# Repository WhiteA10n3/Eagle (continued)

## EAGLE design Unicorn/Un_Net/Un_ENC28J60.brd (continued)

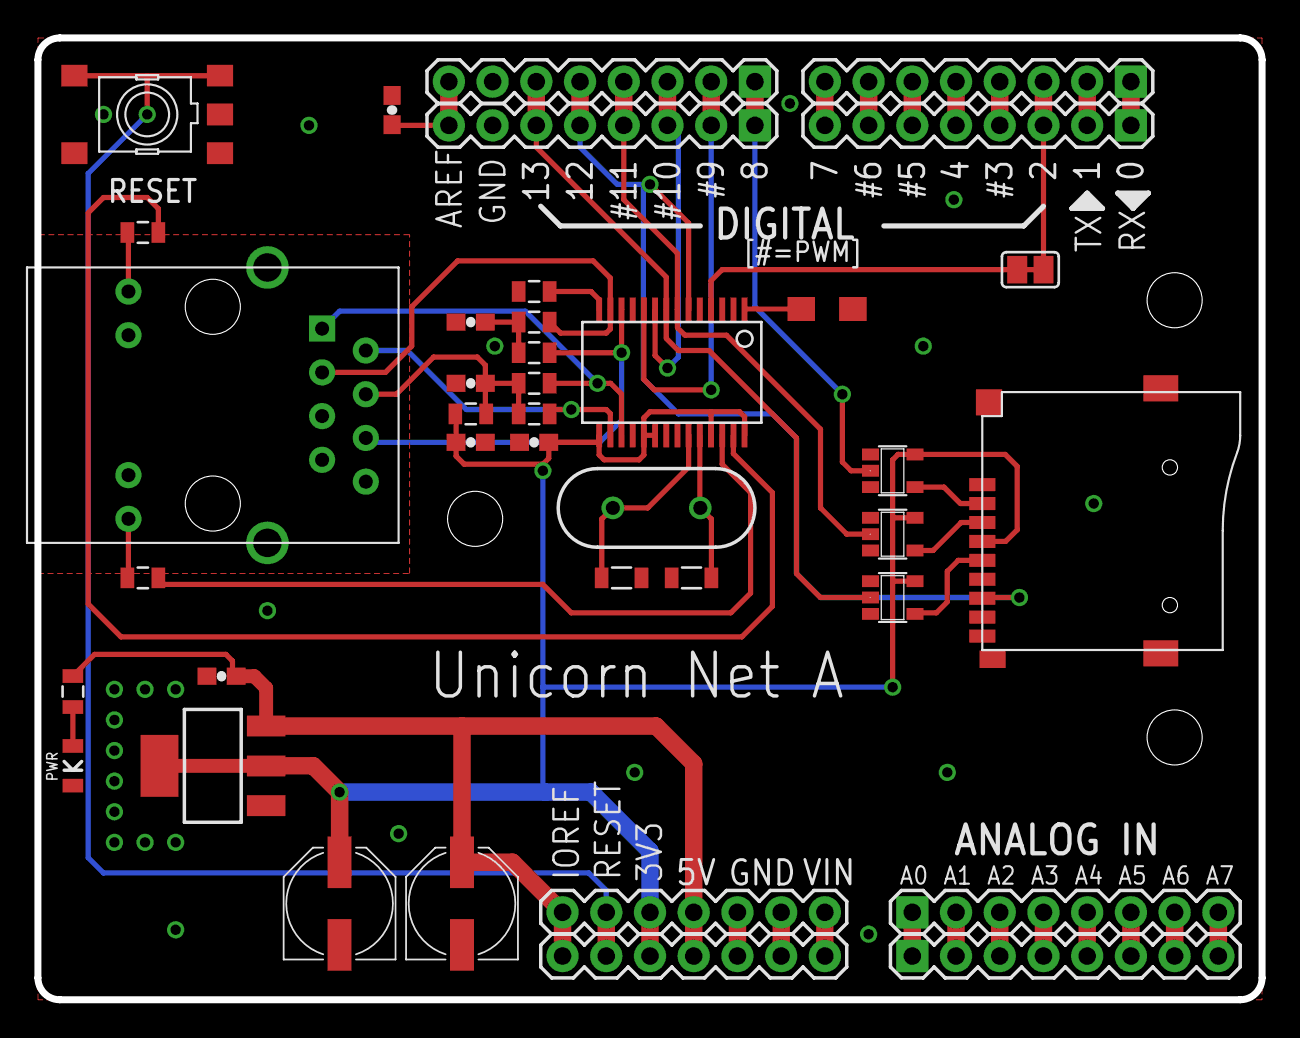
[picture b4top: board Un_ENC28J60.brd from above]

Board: 2 copper layers, 71.1 x 55.9 mm, 39 parts (0 on the bottom side), 46 nets.

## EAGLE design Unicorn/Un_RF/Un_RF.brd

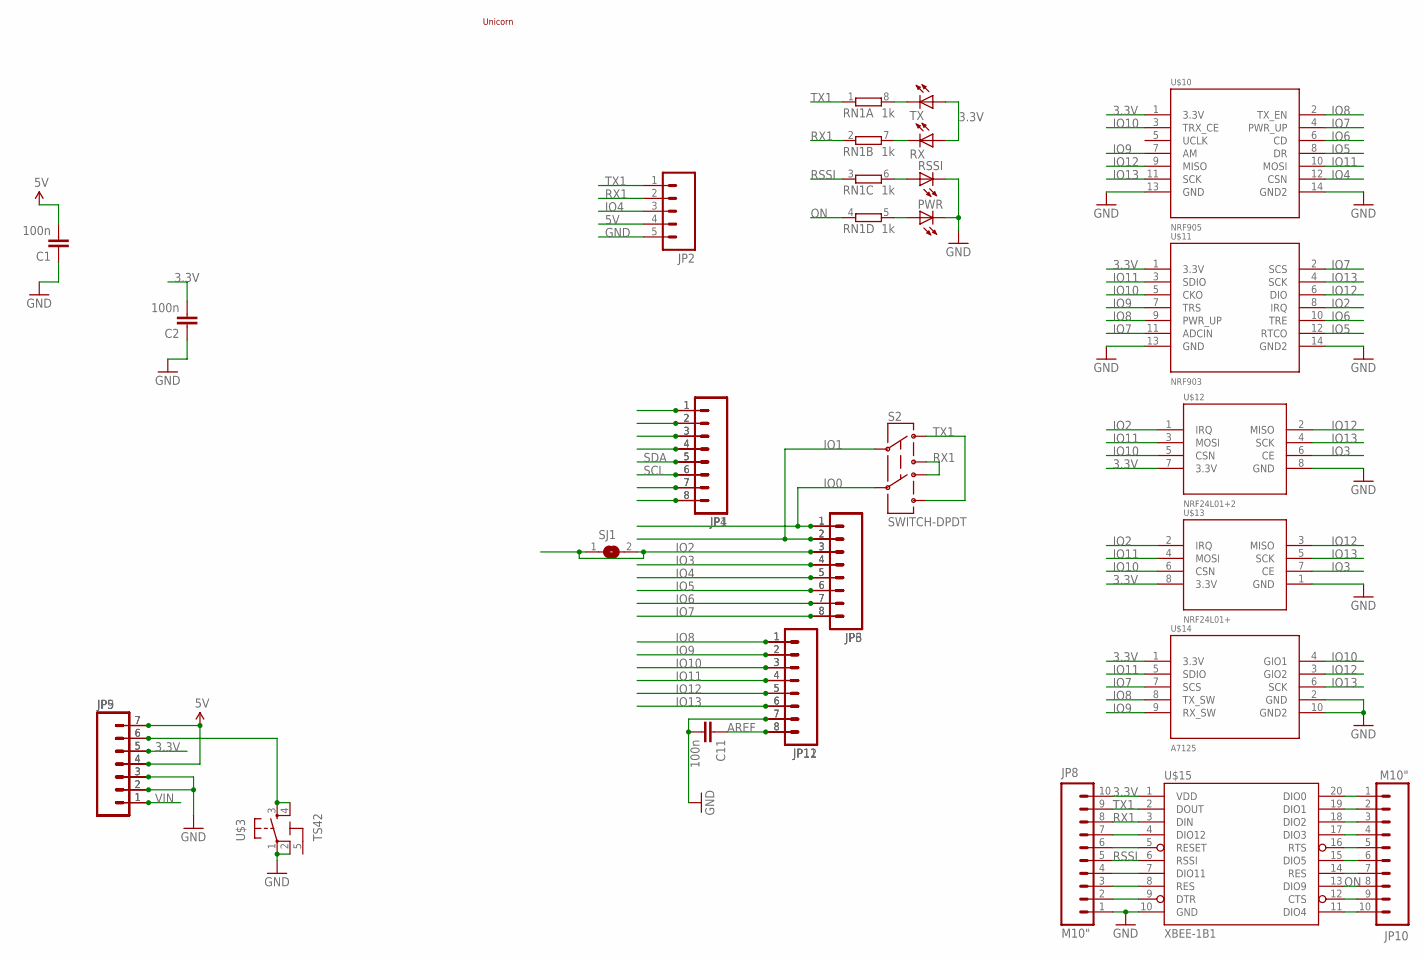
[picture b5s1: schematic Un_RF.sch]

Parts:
C1, C2, C11: 100n; 0603-CAP
JP1, JP4, JP11, JP12: M081X08; 1X08
JP2: M05PTH; 1X05
JP3, JP6: M08; 1X08
JP5, JP9: M07; 1X07
JP8, JP10: M10"; 1X10
PWR: LED0805; LED-0805
RN1: 1k; CAY16
RSSI: LED0805; LED-0805
RX: LED0805; LED-0805
S2: SWITCH-DPDT; SWITCH-P2
SJ1: SJ
TX: LED0805; LED-0805
U$3: TS42
U$4: UNICORN; UNICORN_1
U$10: NRF905; 2X7
U$11: NRF903; 2X7
U$12: NRF24L01+2; 2X4
U$13: NRF24L01+; 1X08
U$14: A7125; 1X10-2MM
U$15: XBEE-1B1; XBEE-1

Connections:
3.3V: C2.2, JP5.5, JP8.10, JP9.5, RX.1 (A), TX.1 (A), U$10.1 (3.3V), U$11.1 (3.3V), U$12.7 (3.3V), U$13.8 (3.3V), U$14.1 (3.3V), U$15.1 (VDD)
5V: C1.2, JP2.4, JP5.4, JP5.7, JP9.4, JP9.7
A0: JP1.1, JP4.1
AREF: C11.1, JP11.8, JP12.8
GND: C1.1, C2.1, C11.2, JP2.5, JP5.2, JP5.3, JP8.1, JP9.2, JP9.3, JP11.7, JP12.7, PWR.2 (C), RSSI.2 (C), U$3.1, U$3.2, U$10.13 (GND), U$10.14 (GND2), U$11.13 (GND), U$11.14 (GND2), U$12.8 (GND), U$13.1 (GND), U$14.2 (GND), U$14.10 (GND2), U$15.10 (GND)
IO0: JP3.1, JP6.1, S2.5
IO1: JP3.2, JP6.2, S2.2
IO2: JP3.3, JP6.3, SJ1.1, SJ1.2, U$11.8 (IRQ), U$12.1 (IRQ), U$13.2 (IRQ)
IO3: JP3.4, JP6.4, U$12.6 (CE), U$13.7 (CE)
IO4: JP2.3, JP3.5, JP6.5, U$10.12 (CSN)
IO5: JP3.6, JP6.6, U$10.8 (DR), U$11.12 (RTCO)
IO6: JP3.7, JP6.7, U$10.6 (CD), U$11.10 (TRE)
IO7: JP3.8, JP6.8, U$10.4 (PWR_UP), U$11.2 (SCS), U$11.11 (ADCIN), U$14.7 (SCS)
IO8: JP11.1, JP12.1, U$10.2 (TX_EN), U$11.9 (PWR_UP), U$14.8 (TX_SW)
IO9: JP11.2, JP12.2, U$10.7 (AM), U$11.7 (TRS), U$14.9 (RX_SW)
IO10: JP11.3, JP12.3, U$10.3 (TRX_CE), U$11.5 (CKO), U$12.5 (CSN), U$13.6 (CSN), U$14.4 (GIO1)
IO11: JP11.4, JP12.4, U$10.10 (MOSI), U$11.3 (SDIO), U$12.3 (MOSI), U$13.4 (MOSI), U$14.5 (SDIO)
IO12: JP11.5, JP12.5, U$10.9 (MISO), U$11.6 (DIO), U$12.2 (MISO), U$13.3 (MISO), U$14.3 (GIO2)
IO13: JP11.6, JP12.6, U$10.11 (SCK), U$11.4 (SCK), U$12.4 (SCK), U$13.5 (SCK), U$14.6 (SCK)
unnamed: RN1.8 (2), TX.2 (C)
unnamed: RN1.7 (2), RX.2 (C)
unnamed: RN1.6 (2), RSSI.1 (A)
unnamed: PWR.1 (A), RN1.5 (2)
unnamed: JP10.1, U$15.20 (DIO0)
unnamed: JP1.7, JP4.7
unnamed: JP1.8, JP4.8
unnamed: JP10.2, U$15.19 (DIO1)
unnamed: JP10.3, U$15.18 (DIO2)
unnamed: JP10.4, U$15.17 (DIO3)
unnamed: JP1.2, JP4.2
unnamed: JP1.3, JP4.3
unnamed: JP1.4, JP4.4
unnamed: JP10.5, U$15.16 (RTS)
unnamed: JP10.6, U$15.15 (DIO5)
unnamed: JP10.7, U$15.14 (RES)
unnamed: JP5.6, JP9.6, U$3.3, U$3.4
unnamed: JP10.9, U$15.12 (CTS)
unnamed: JP10.10, U$15.11 (DIO4)
unnamed: JP8.2, U$15.9 (DTR)
unnamed: JP8.3, U$15.8 (RES)
unnamed: JP8.4, U$15.7 (DIO11)
unnamed: JP8.6, U$15.5 (RESET)
unnamed: JP8.7, U$15.4 (DIO12)
ON: JP10.8, RN1.4 (1), U$15.13 (DIO9)
RSSI: JP8.5, RN1.3 (1), U$15.6 (RSSI)
RX1: JP2.2, JP8.8, RN1.2 (1), S2.3, S2.4, U$15.3 (DIN)
SCL: JP1.6, JP4.6
SDA: JP1.5, JP4.5
TX1: JP2.1, JP8.9, RN1.1, S2.1, S2.6, U$15.2 (DOUT)
VIN: JP5.1, JP9.1

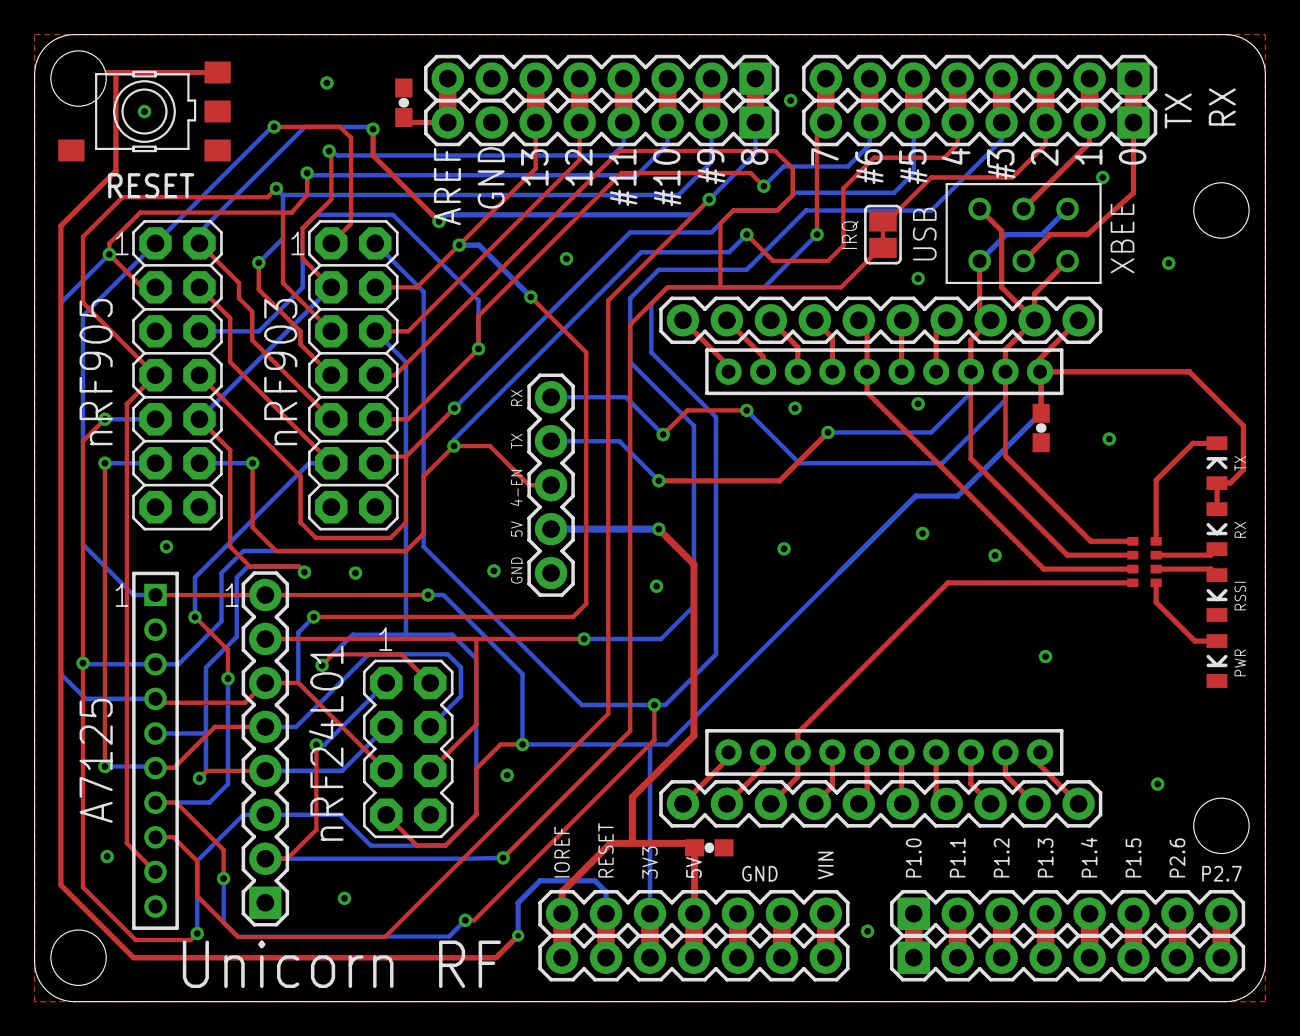
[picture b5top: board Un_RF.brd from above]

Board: 2 copper layers, 71.1 x 55.9 mm, 29 parts (0 on the bottom side), 50 nets.

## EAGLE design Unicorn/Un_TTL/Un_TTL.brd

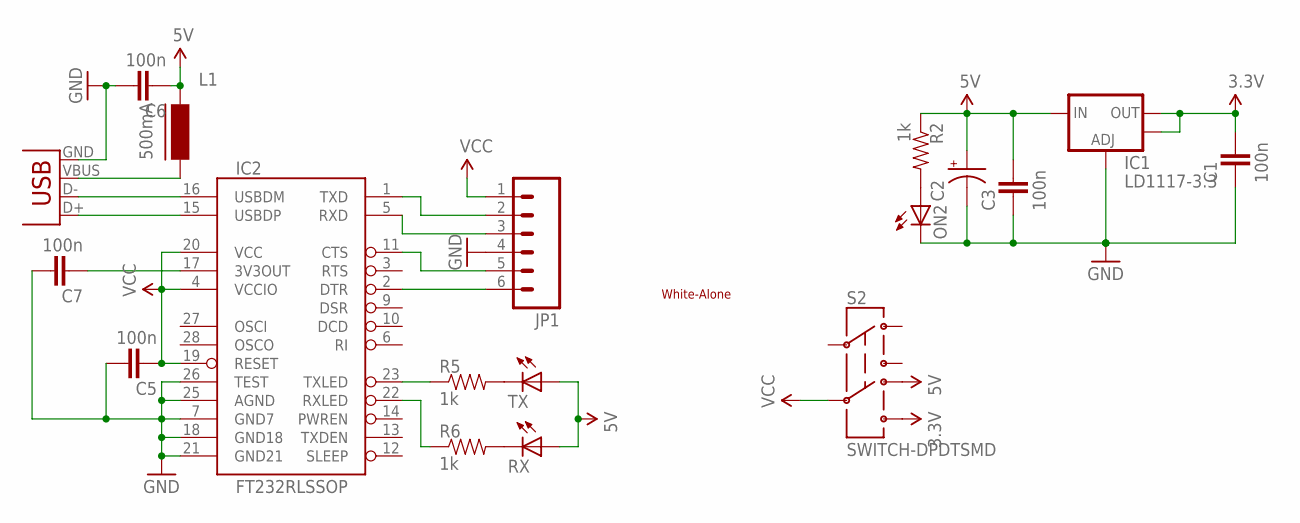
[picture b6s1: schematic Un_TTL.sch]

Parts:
C1, C3, C5, C6, C7: 100n; 0603-CAP
C2: CAP_POL1206; EIA3216
IC1: LD1117-3.3; SOT223
IC2: FT232RLSSOP; SSOP28DB
JP1: M06SIP; 1X06
L1: 500mA; FB805
ON2: LED0805; LED-0805
R2, R5, R6: 1k; 0603-RES
RX: LED0805; LED-0805
S2: SWITCH-DPDTSMD; AYZ0202
TX: LED0805; LED-0805
U$2: WHITE-ALONE_0
X1: USBSMD; USB-MINIB

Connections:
3.3V: C1.1, IC1.2 (OUT), IC1.4 (OUT), S2.6
5V: C2.A (+), C3.1, C6.2, IC1.3 (IN), L1.1, R2.1, RX.1 (A), S2.4, TX.1 (A)
DTR: IC2.11 (CTS), JP1.5
GND: C1.2, C2.C (-), C3.2, C5.1, C6.1, C7.1, IC1.1 (ADJ), IC2.7 (GND7), IC2.18 (GND18), IC2.21 (GND21), IC2.25 (AGND), IC2.26 (TEST), JP1.4, ON2.2 (C), X1.GND
unnamed: ON2.1 (A), R2.2
unnamed: L1.2, X1.VBUS
unnamed: IC2.2 (DTR), JP1.6
unnamed: IC2.16 (USBDM), X1.D-
unnamed: IC2.15 (USBDP), X1.D+
unnamed: IC2.23 (TXLED), R5.1
unnamed: R5.2, TX.2 (C)
unnamed: R6.2, RX.2 (C)
unnamed: IC2.22 (RXLED), R6.1
unnamed: C7.2, IC2.17 (3V3OUT)
RXD: IC2.5 (RXD), JP1.3
TXD: IC2.1 (TXD), JP1.2
VCC: C5.2, IC2.4 (VCCIO), IC2.19 (RESET), IC2.20 (VCC), JP1.1, S2.5

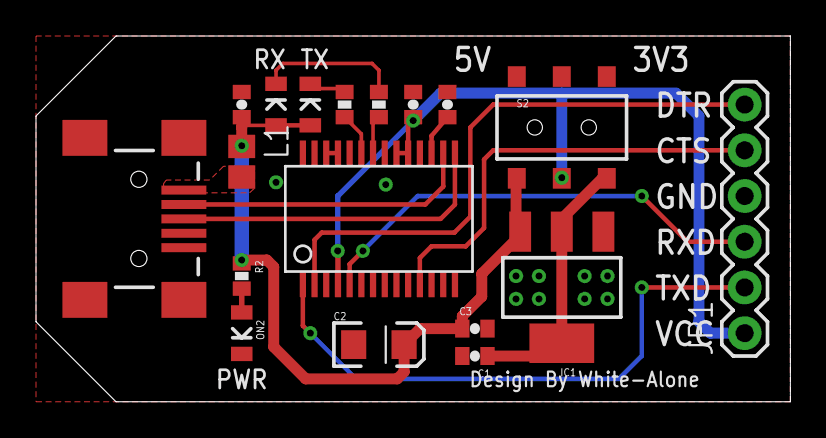
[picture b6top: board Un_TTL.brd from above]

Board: 2 copper layers, 41.9 x 20.3 mm, 19 parts (1 on the bottom side), 17 nets.

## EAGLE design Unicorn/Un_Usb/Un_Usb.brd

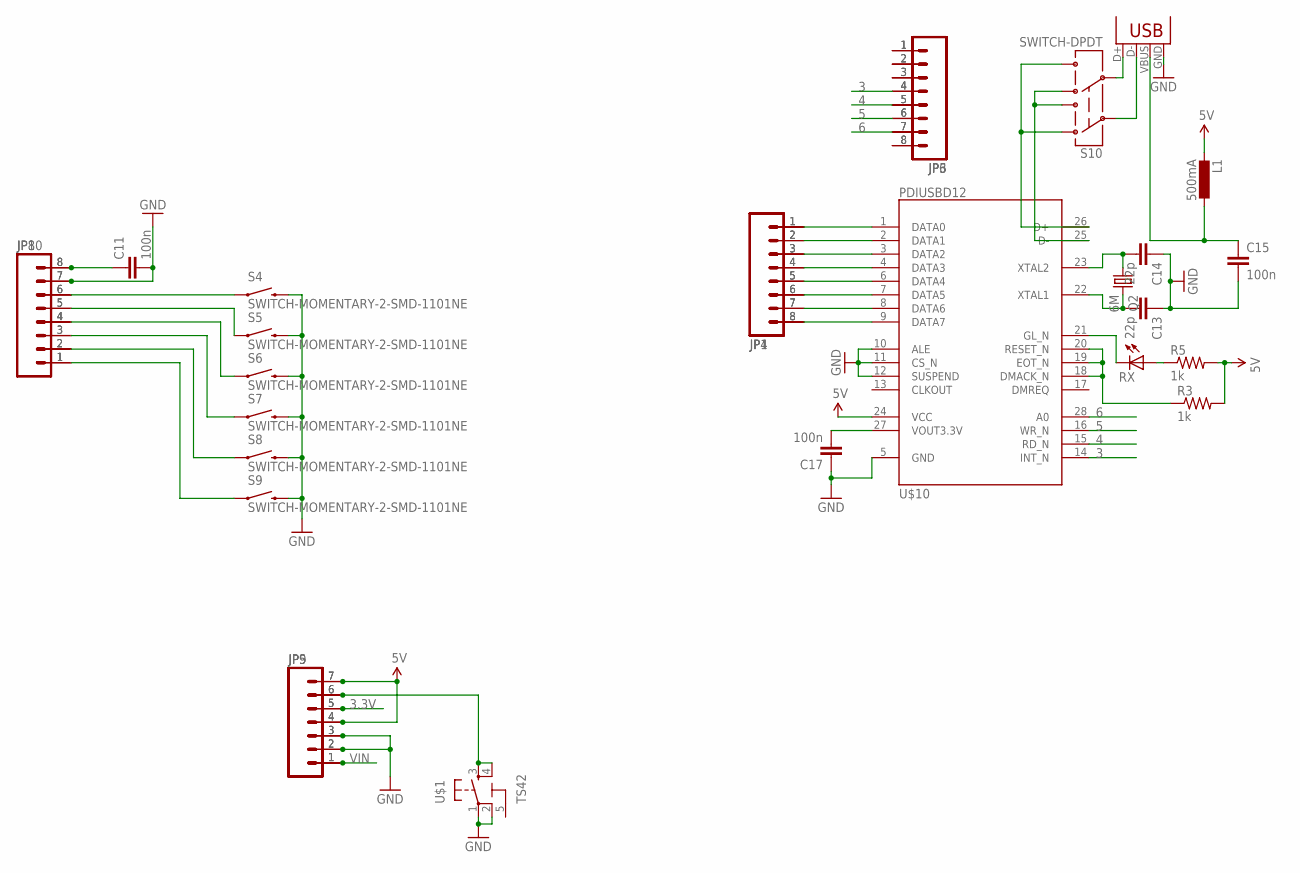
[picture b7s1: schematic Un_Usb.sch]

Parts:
C11, C15, C17: 100n; 0603-CAP
C13, C14: 22p; 0805
JP1, JP4: M081X08; 1X08
JP3, JP6, JP8, JP10: M08; 1X08
JP5, JP9: M07; 1X07
L1: 500mA; L1812
Q2: 6M; HC49US
R3, R5: 1k; 0805
RX: LED0805; LED-0805
S4, S5, S6, S7, S8, S9: SWITCH-MOMENTARY-2-SMD-1101NE; TACTILE-SWITCH-1101NE
S10: SWITCH-DPDT; SWITCH-P2
U$1: TS42
U$10: PDIUSBD12; TSSOP28
X2: USB; USB-A-M

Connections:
2: JP3.3, JP6.3
3: JP3.4, JP6.4, U$10.14 (INT_N)
3.3V: JP5.5, JP9.5
4: JP3.5, JP6.5, U$10.15 (RD_N)
5: JP3.6, JP6.6, U$10.16 (WR_N)
5V: JP5.4, JP5.7, JP9.4, JP9.7, L1.2, R3.2, R5.2, U$10.24 (VCC)
6: JP3.7, JP6.7, U$10.28 (A0)
A0: JP1.1, JP4.1, U$10.1 (DATA0)
AREF: C11.1, JP8.8, JP10.8
D+: S10.1, S10.6, U$10.26 (D+)
D-: S10.3, S10.4, U$10.25 (D-)
GND: C11.2, C13.1, C14.1, C15.2, C17.1, JP5.2, JP5.3, JP8.7, JP9.2, JP9.3, JP10.7, S4.P$2 (2), S5.P$2 (2), S6.P$2 (2), S7.P$2 (2), S8.P$2 (2), S9.P$2 (2), U$1.1, U$1.2, U$10.5 (GND), U$10.10 (ALE), U$10.11 (CS_N), U$10.12 (SUSPEND), X2.GND
IO0: JP3.1, JP6.1
unnamed: JP1.8, JP4.8, U$10.9 (DATA7)
unnamed: JP3.8, JP6.8
unnamed: JP1.7, JP4.7, U$10.8 (DATA6)
unnamed: JP1.6, JP4.6, U$10.7 (DATA5)
unnamed: JP1.5, JP4.5, U$10.6 (DATA4)
unnamed: R5.1, RX.1 (A)
unnamed: JP1.4, JP4.4, U$10.4 (DATA3)
unnamed: JP8.1, JP10.1, S9.P$1 (1)
unnamed: JP8.2, JP10.2, S8.P$1 (1)
unnamed: JP8.3, JP10.3, S7.P$1 (1)
unnamed: JP8.5, JP10.5, S5.P$1 (1)
unnamed: JP8.6, JP10.6, S4.P$1 (1)
unnamed: JP8.4, JP10.4, S6.P$1 (1)
unnamed: C15.1, L1.1, X2.VBUS
unnamed: C13.2, Q2.2, U$10.22 (XTAL1)
unnamed: JP3.2, JP6.2
unnamed: C14.2, Q2.1, U$10.23 (XTAL2)
unnamed: JP1.2, JP4.2, U$10.2 (DATA1)
unnamed: JP1.3, JP4.3, U$10.3 (DATA2)
unnamed: C17.2, U$10.27 (VOUT3.3V)
unnamed: RX.2 (C), U$10.21 (GL_N)
unnamed: R3.1, U$10.18 (DMACK_N), U$10.19 (EOT_N), U$10.20 (RESET_N)
unnamed: JP5.6, JP9.6, U$1.3, U$1.4
UD+: S10.5, X2.D+
UD-: S10.2, X2.D-
VIN: JP5.1, JP9.1

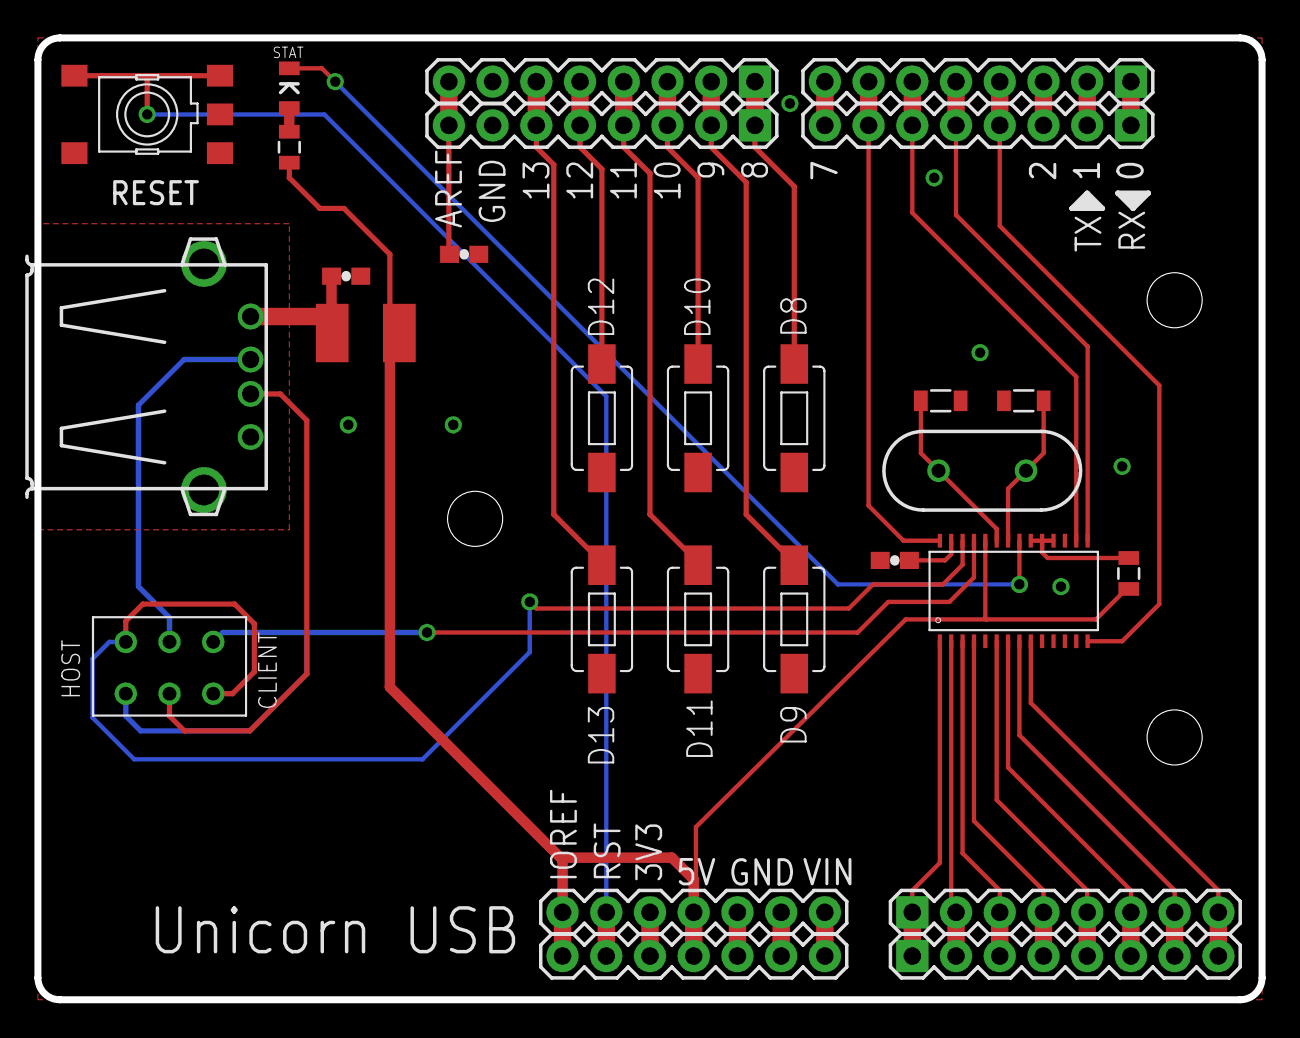
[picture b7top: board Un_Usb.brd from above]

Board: 2 copper layers, 71.1 x 55.9 mm, 28 parts (0 on the bottom side), 39 nets.

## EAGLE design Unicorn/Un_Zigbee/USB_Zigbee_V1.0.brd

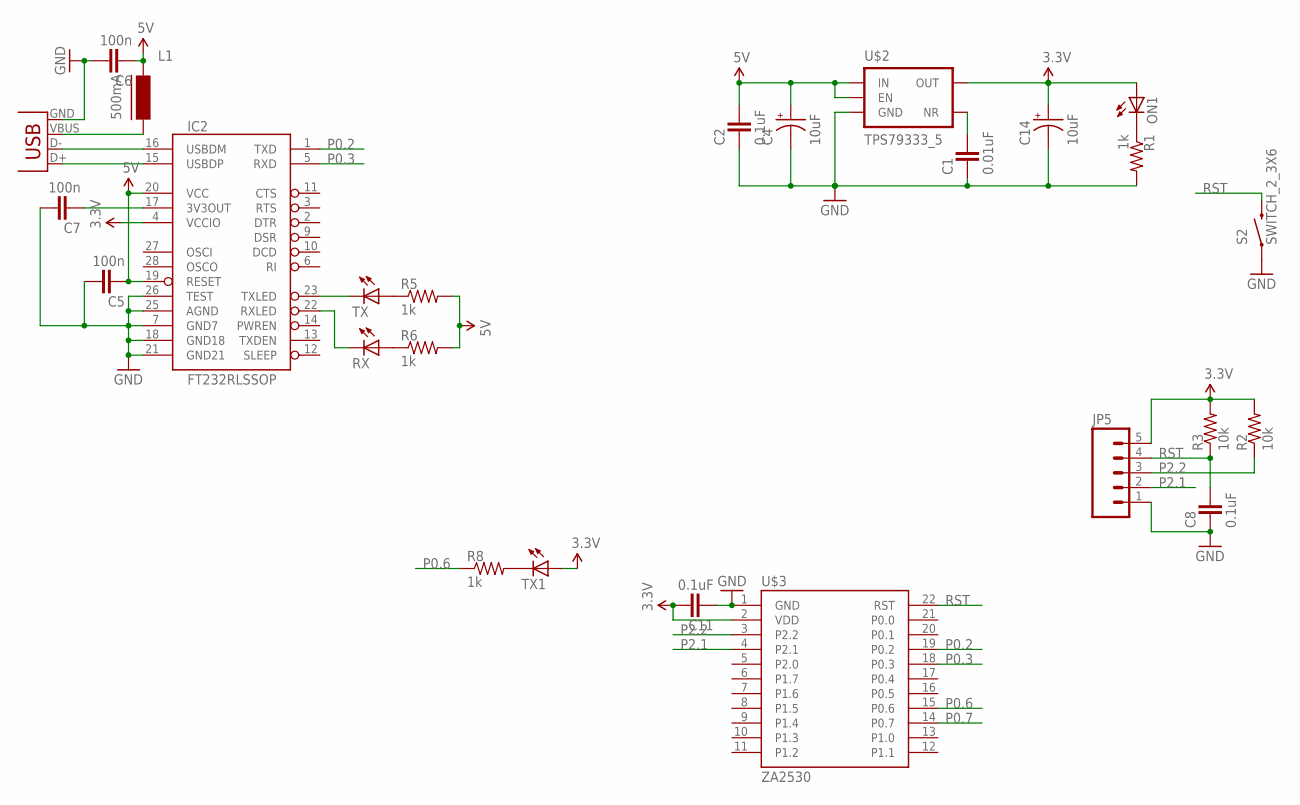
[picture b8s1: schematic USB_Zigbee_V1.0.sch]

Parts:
C1: 0.01uF; 0603-CAP
C2, C8, C11: 0.1uF; 0603-CAP
C4, C14: 10uF; EIA3216
C5, C6, C7: 100n; 0603-CAP
IC2: FT232RLSSOP; SSOP28DB
JP5: M05PTH; 1X05
L1: 500mA; FB805
ON1: LED0603; LED-0603
R1, R5, R6, R8: 1k; 0603-RES
R2, R3: 10k; 0603-RES
RX: LED0603; LED-0603
S2: SWITCH_2_3X6; TACTILE-SWITCH-1101NE
TX, TX1: LED0603; LED-0603
U$2: TPS79333_5; SOT23-5
U$3: ZA2530
X1: USB_4-A-H_2; USB-A-H_2

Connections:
3.3V: C11.1, C14.A (+), IC2.4 (VCCIO), JP5.5, ON1.A, R2.2, R3.2, TX1.A, U$2.5 (OUT), U$3.2 (VDD)
5V: C2.1, C4.A (+), C5.2, C6.2, IC2.19 (RESET), IC2.20 (VCC), L1.1, R5.2, R6.2, U$2.1 (IN), U$2.3 (EN)
GND: C1.2, C2.2, C4.C (-), C5.1, C6.1, C7.1, C8.2, C11.2, C14.C (-), IC2.7 (GND7), IC2.18 (GND18), IC2.21 (GND21), IC2.25 (AGND), IC2.26 (TEST), JP5.1, R1.2, S2.P$1 (1), U$2.2 (GND), U$3.1 (GND), X1.GND
unnamed: ON1.C, R1.1
unnamed: R5.1, TX.A
unnamed: L1.2, X1.VBUS
unnamed: R8.2, TX1.C
unnamed: IC2.16 (USBDM), X1.D-
unnamed: IC2.15 (USBDP), X1.D+
unnamed: IC2.23 (TXLED), TX.C
unnamed: R6.1, RX.A
unnamed: C1.1, U$2.4 (NR)
unnamed: IC2.22 (RXLED), RX.C
unnamed: C7.2, IC2.17 (3V3OUT)
P0.2: IC2.1 (TXD), U$3.19 (P0.2)
P0.3: IC2.5 (RXD), U$3.18 (P0.3)
P0.6: R8.1, U$3.15 (P0.6)
P0.7: U$3.14 (P0.7)
P2.1: JP5.2, U$3.4 (P2.1)
P2.2: JP5.3, R2.1, U$3.3 (P2.2)
RST: C8.1, JP5.4, R3.1, S2.P$2 (2), U$3.22 (RST)

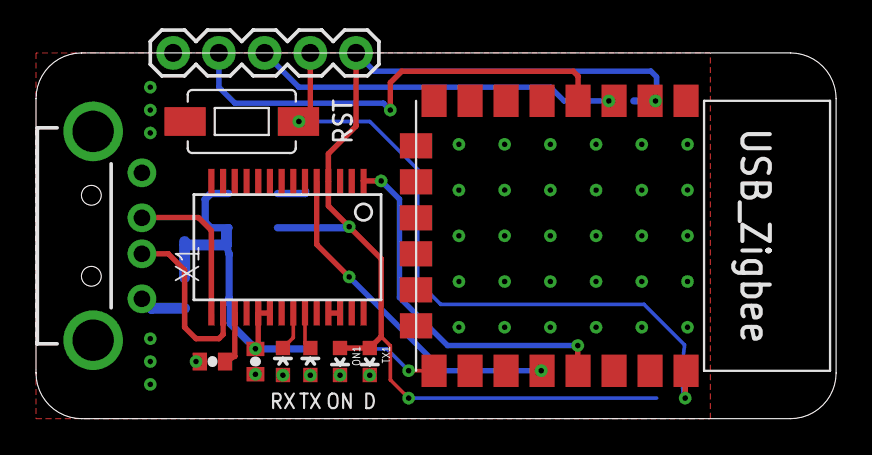
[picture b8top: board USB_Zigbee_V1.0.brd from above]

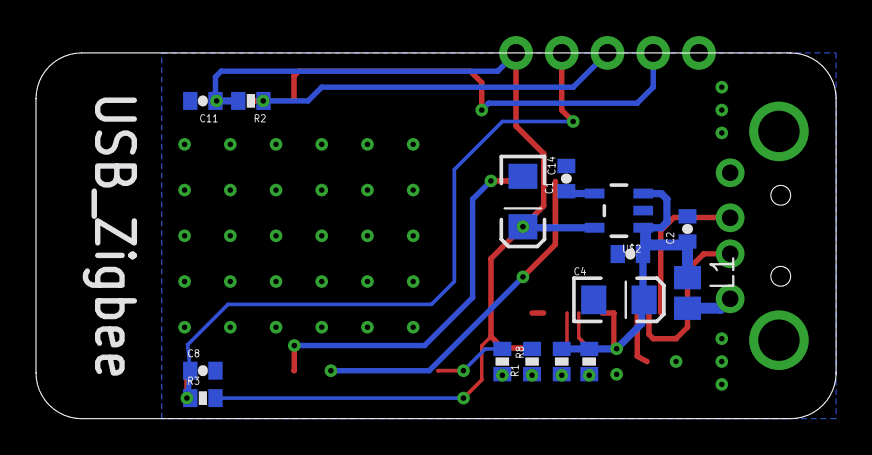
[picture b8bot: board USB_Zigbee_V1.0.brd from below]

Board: 2 copper layers, 44.5 x 20.3 mm, 26 parts (15 on the bottom side), 20 nets.
